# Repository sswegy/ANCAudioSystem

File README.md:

# ANCAudioSystem
## Автомобилна аудио система с активно шумопотискане - Дипломна работа

## Характеристики
- Активно шумопотискане
- Изравняване на звука по 3 честотни ленти
- Изравняване на противошума по 3 честотни ленти
- Bluetooth връзка
- AUX връзка
- Визуализация на метаданните на песните
- Контроли за промяна/пауза на песента

## Използвани технологии
- ESP32-WROOM-32
- C++
- Електроника

[Документация](https://docs.google.com/document/d/18OyuSNhzSNt5vsgb9MGb9Y_gkE6eRHnCl0IYLaxOIx8/edit?usp=sharing)

## Автор
[Виктор Велков](https://www.github.com/sswegy) 

Произведено во Света Троица

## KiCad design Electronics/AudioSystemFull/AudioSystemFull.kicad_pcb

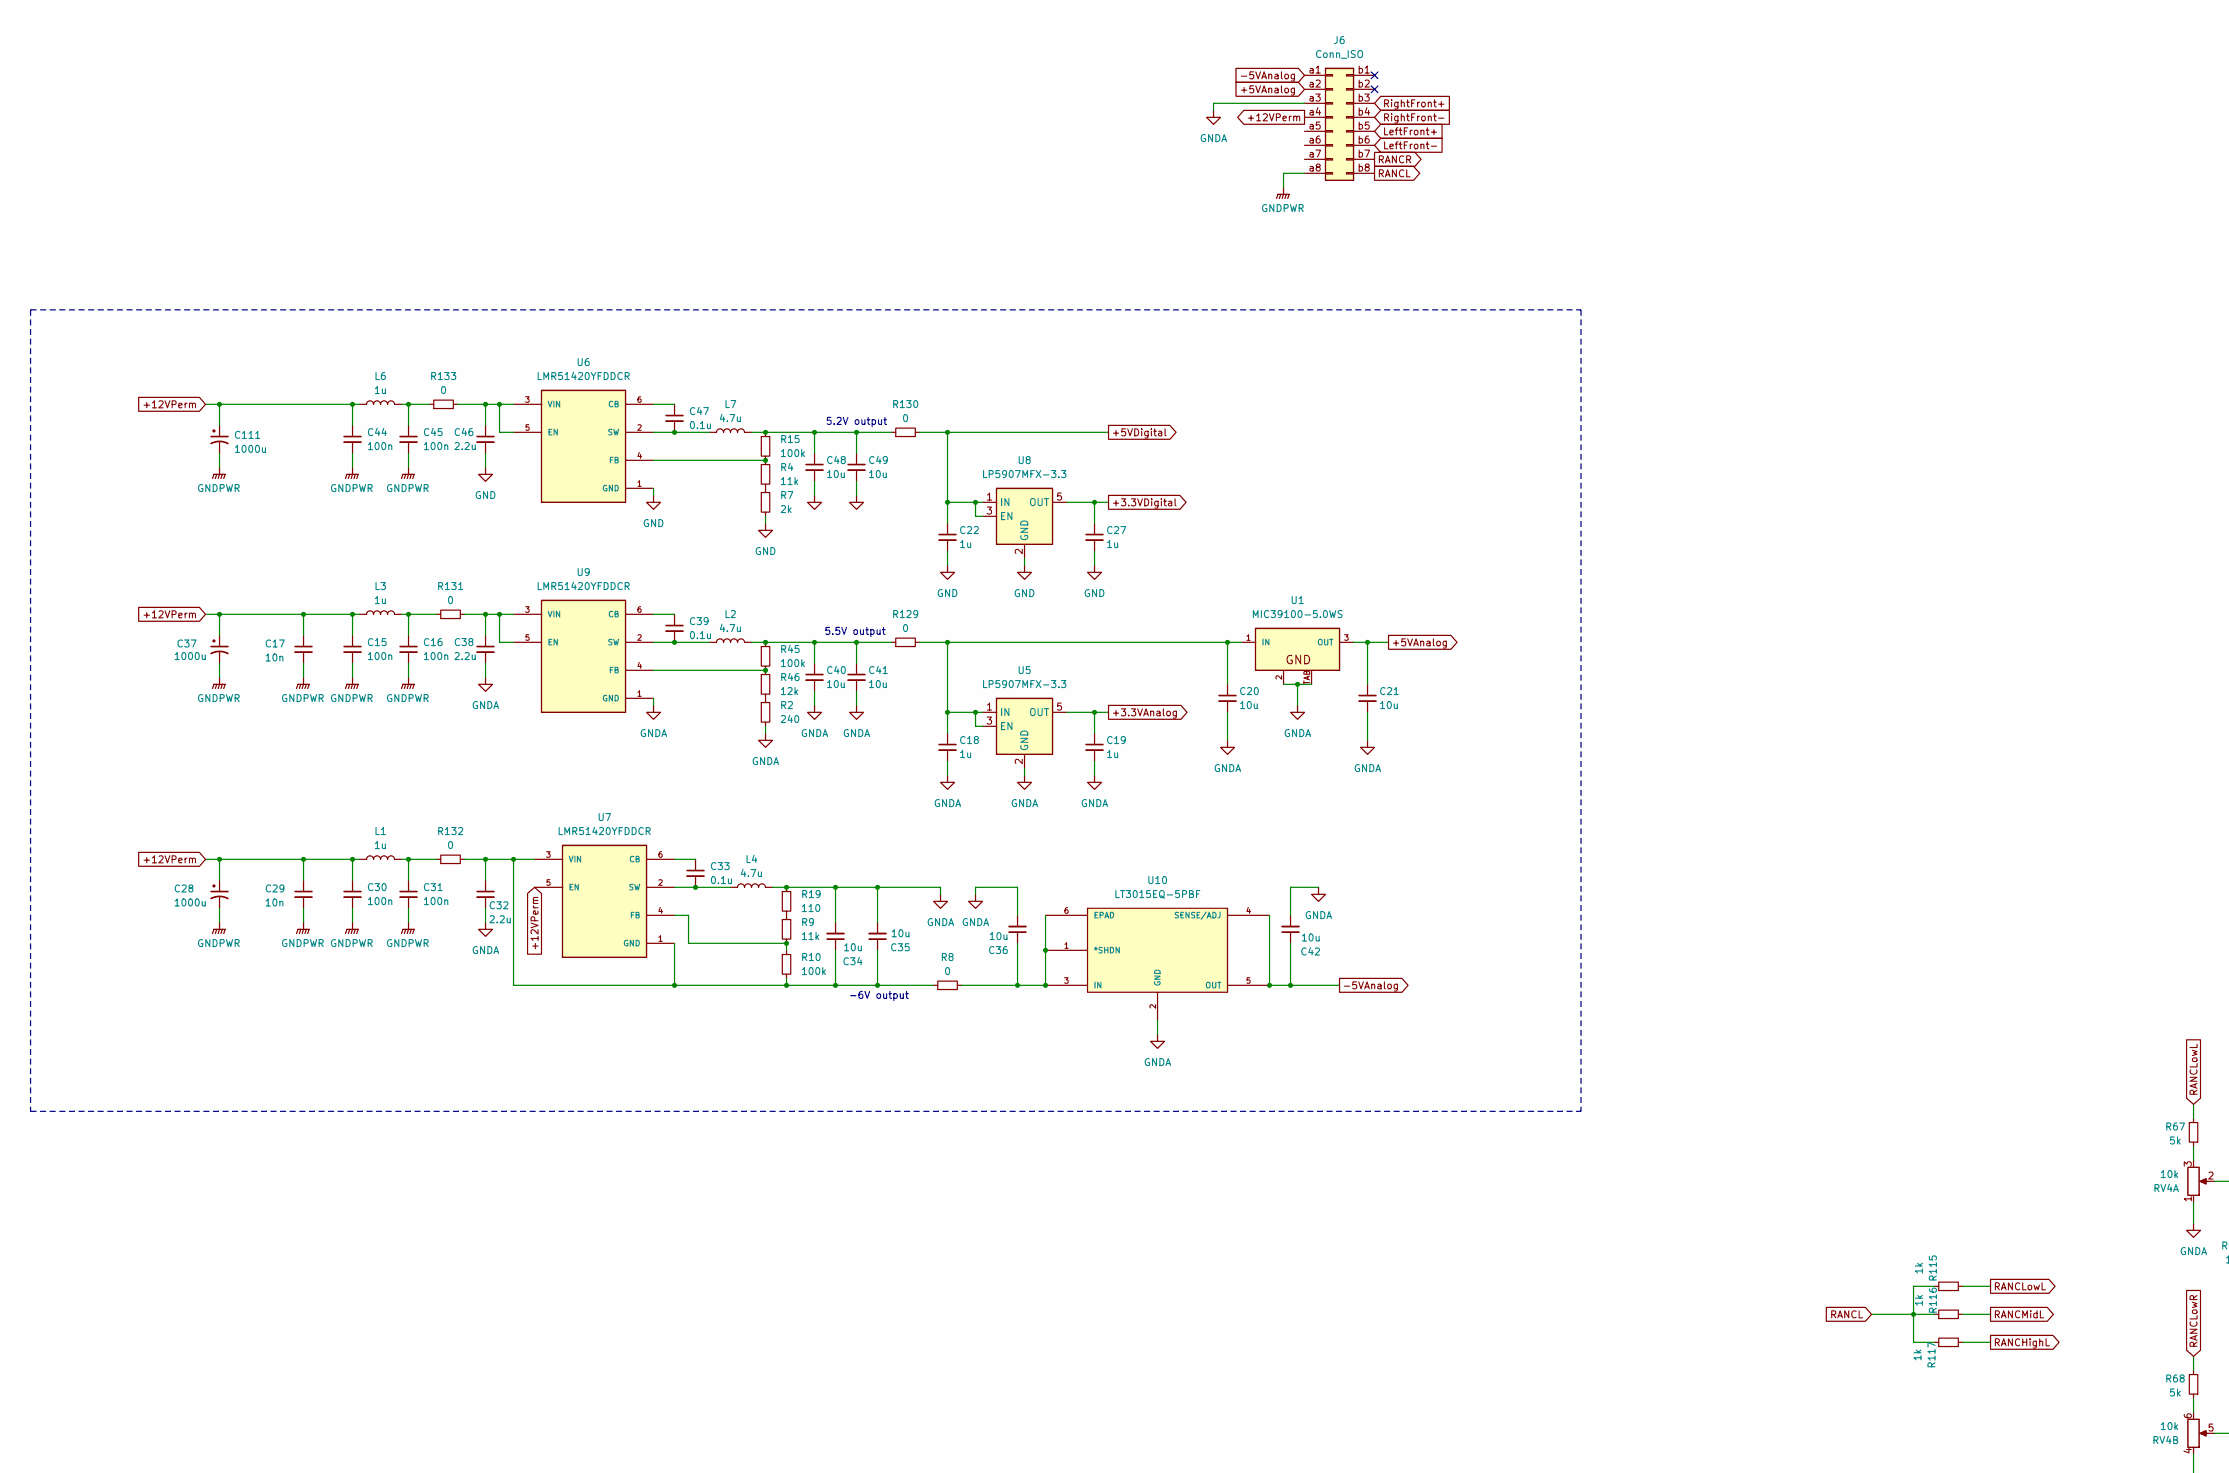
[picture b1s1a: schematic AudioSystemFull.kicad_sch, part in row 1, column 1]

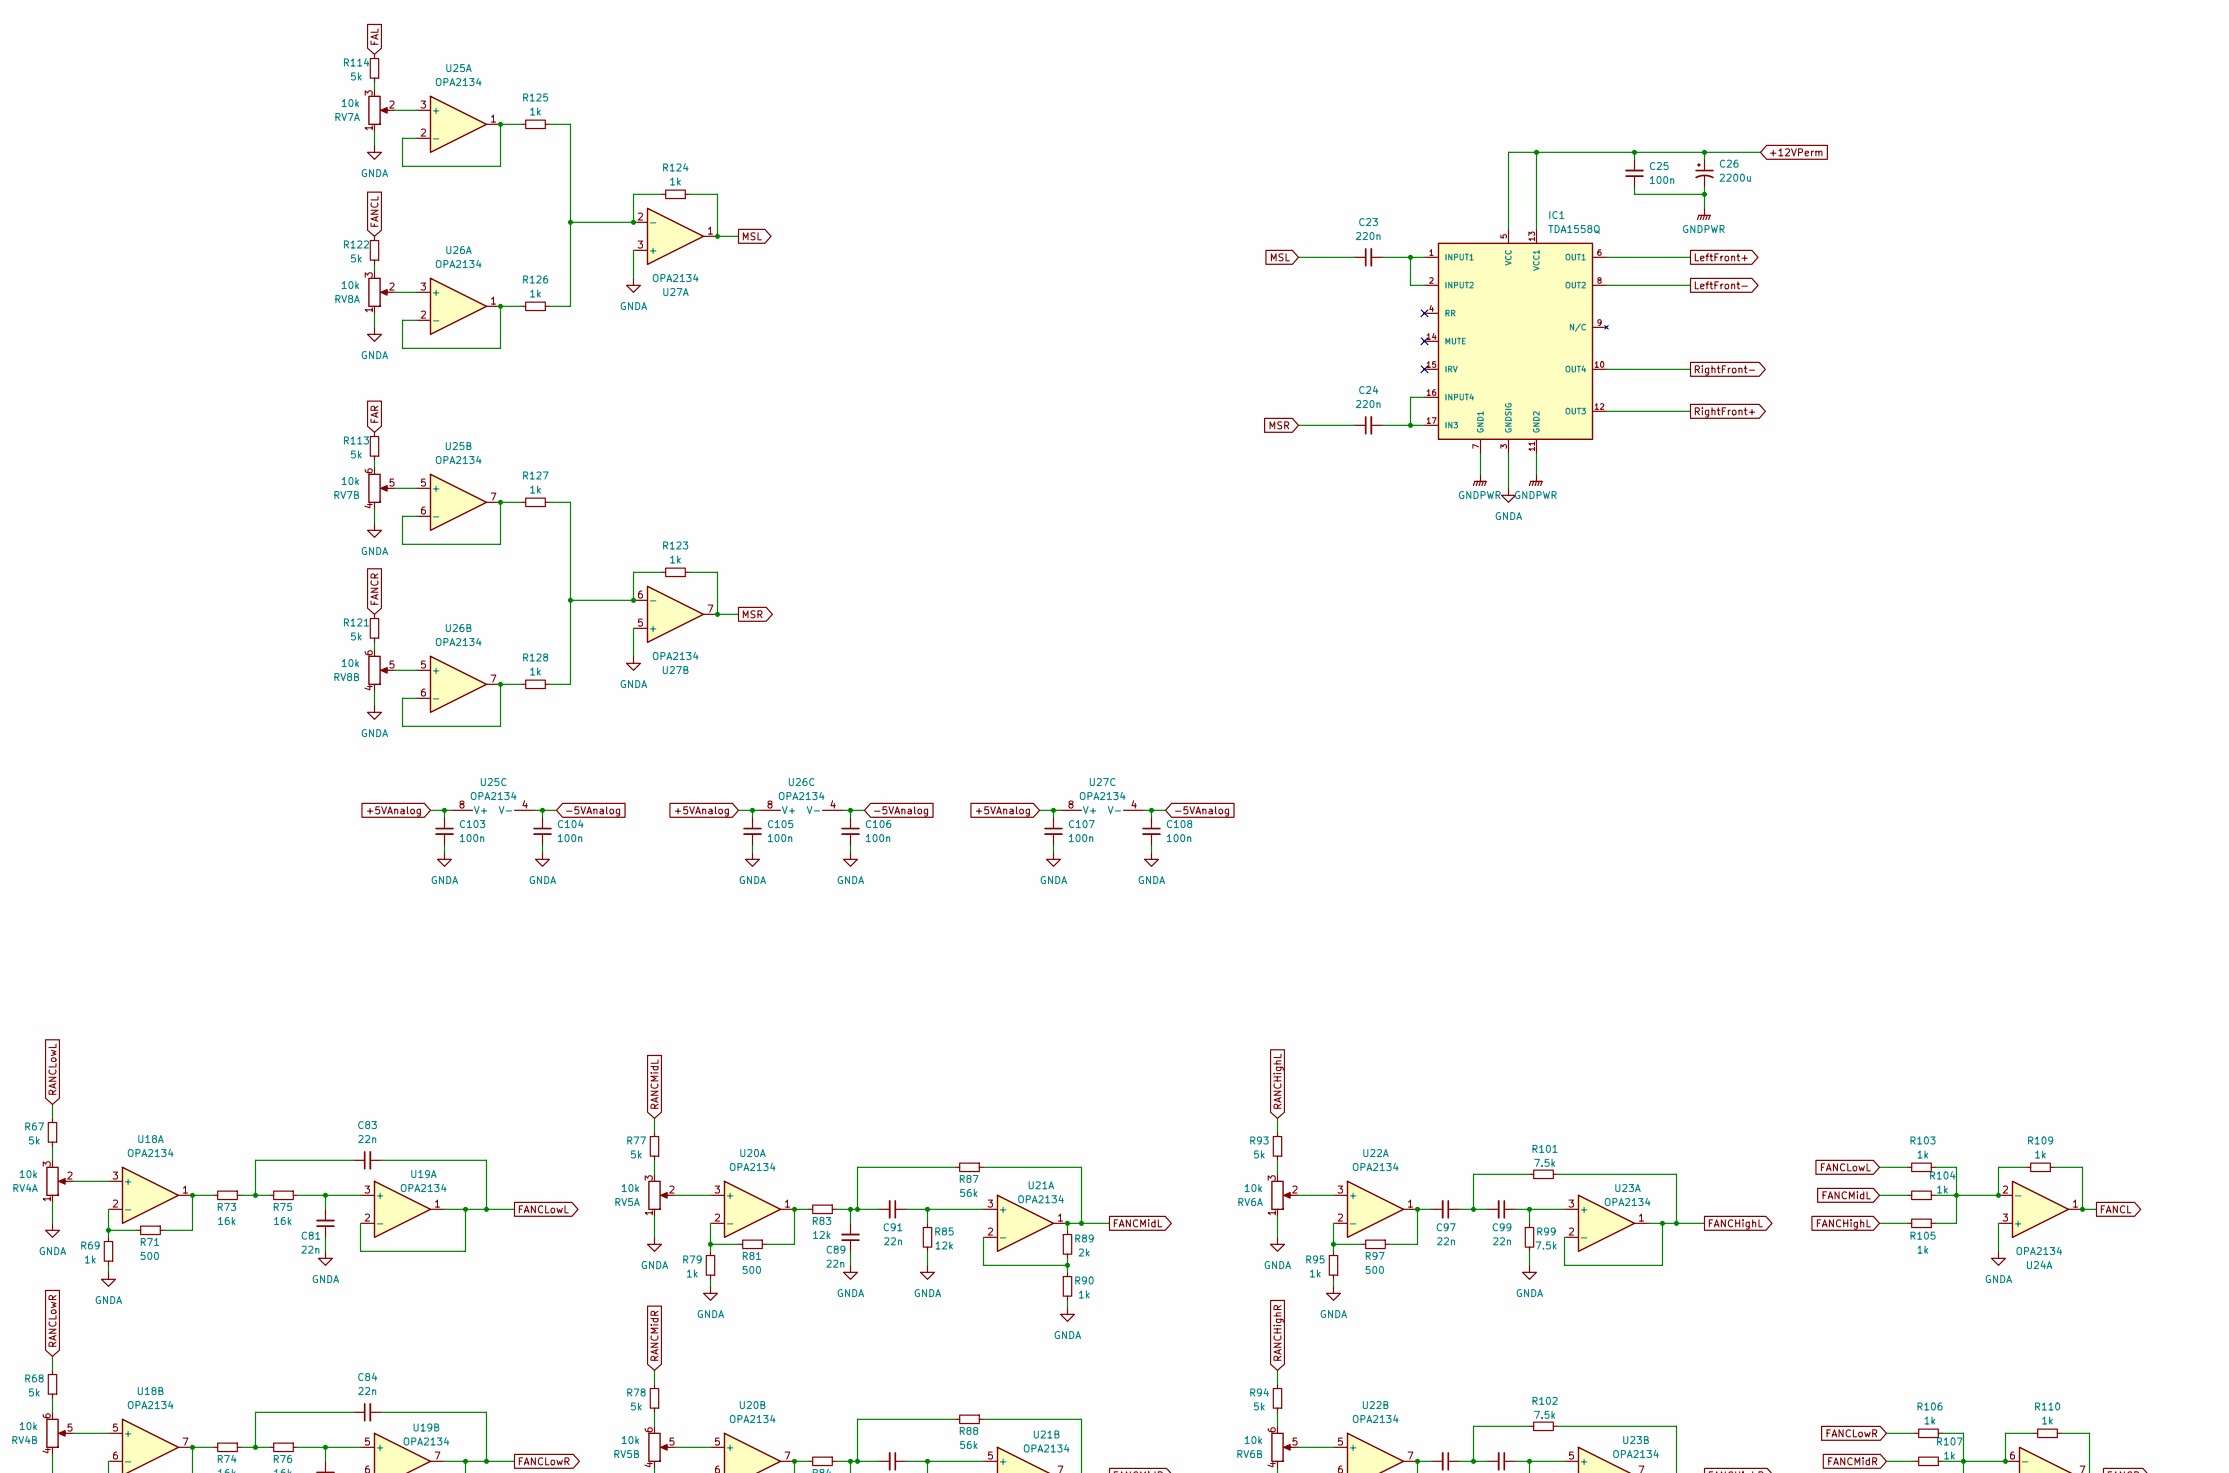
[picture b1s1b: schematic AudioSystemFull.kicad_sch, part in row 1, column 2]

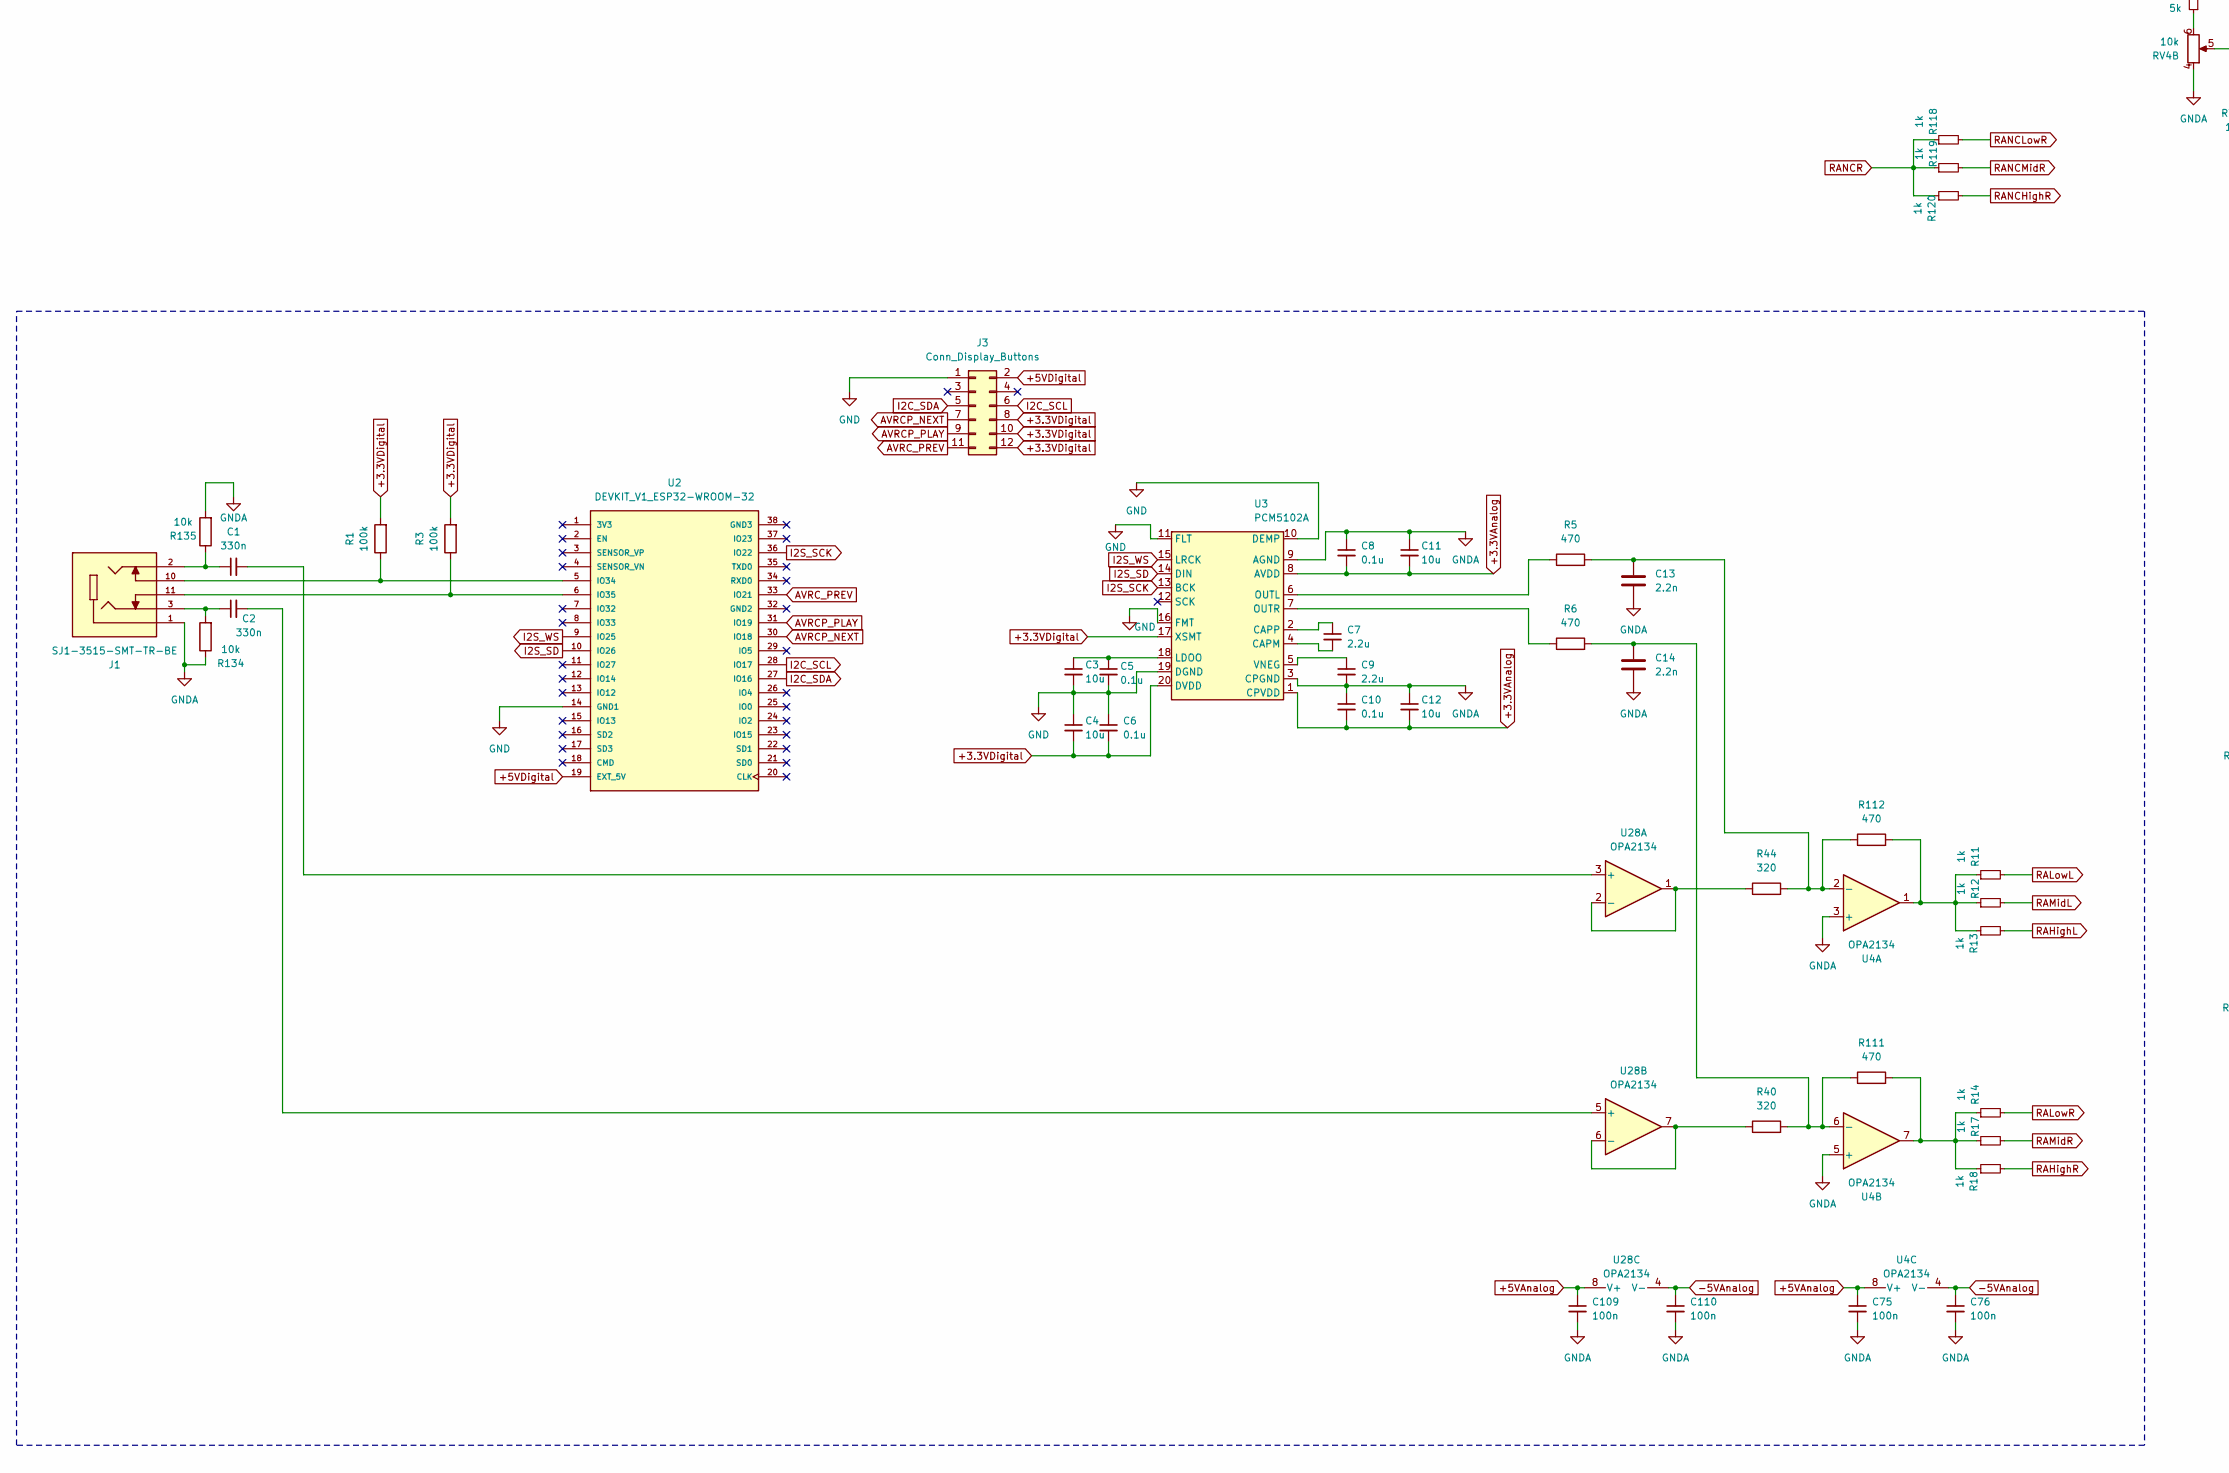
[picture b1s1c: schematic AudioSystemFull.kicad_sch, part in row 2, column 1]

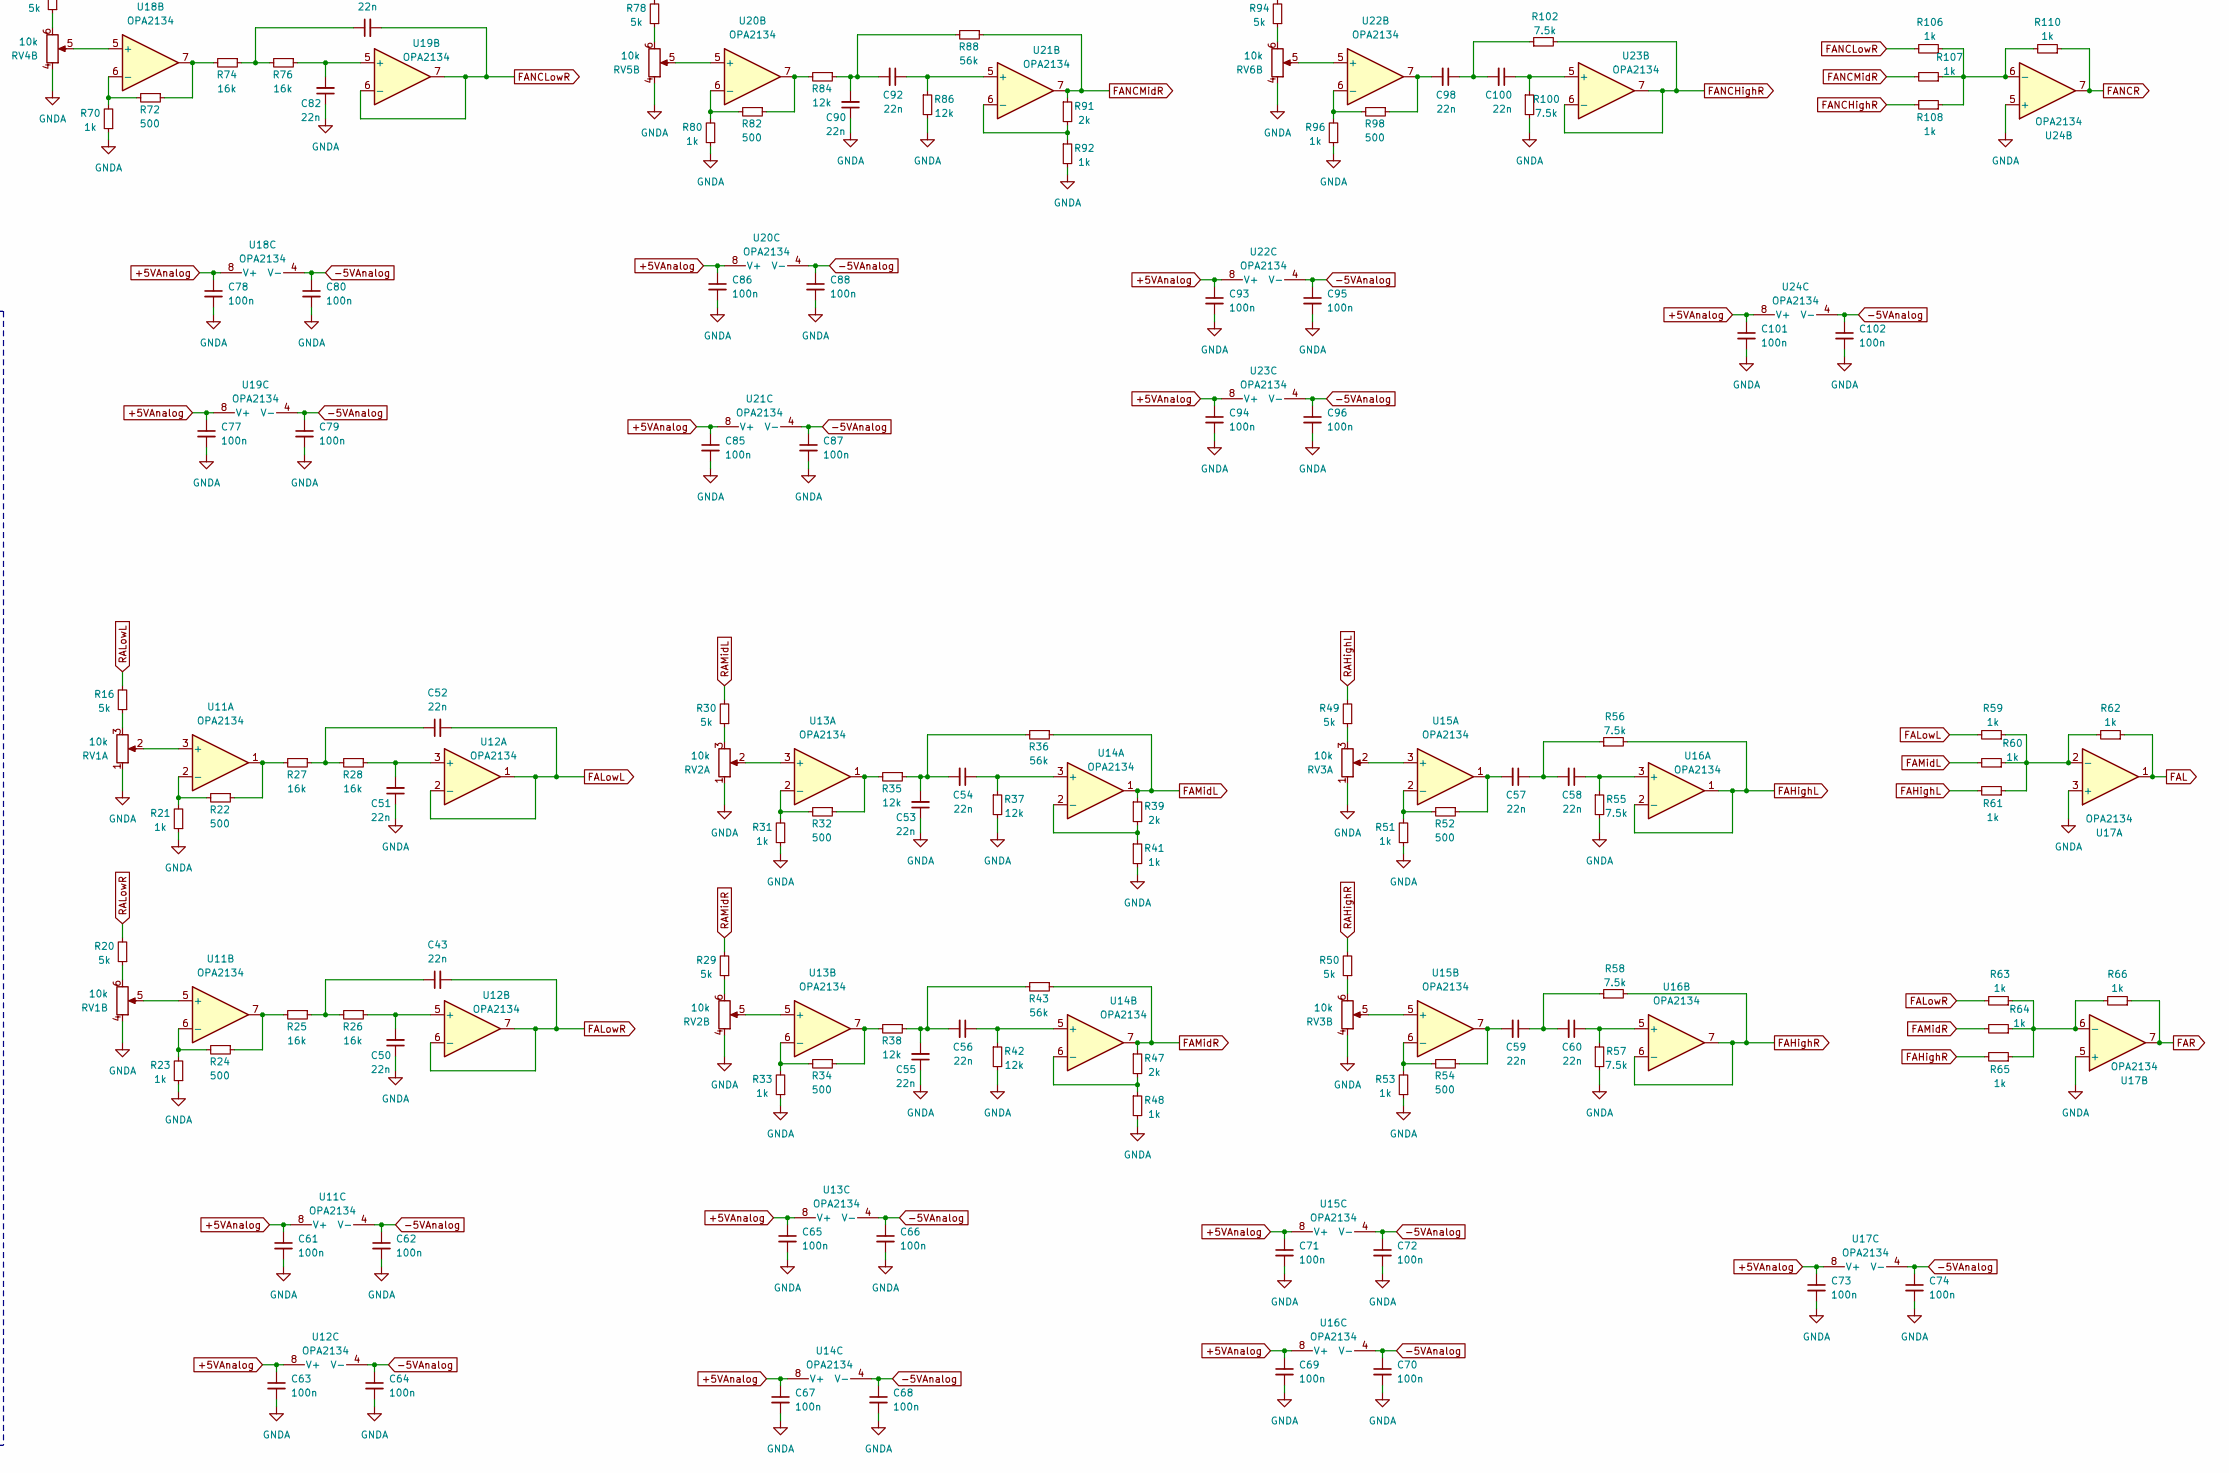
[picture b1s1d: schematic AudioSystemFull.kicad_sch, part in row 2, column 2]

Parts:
C1, C2: 330n; C_1206_3216Metric_Pad1.33x1.80mm_HandSolder; MANUFACTURER_PART_NUMBER GRM31C5C1E334JE01L
C3, C4, C11, C12, C20, C21, C34, C35, C36, C40, C41, C42, C48, C49: 10u; C_0805_2012Metric_Pad1.18x1.45mm_HandSolder; MANUFACTURER_PART_NUMBER GRM21BZ71E106KE15K
C5, C6, C8, C10, C33, C39, C47: 0.1u; C_0805_2012Metric_Pad1.18x1.45mm_HandSolder; MANUFACTURER_PART_NUMBER C0805C104K3RACTU
C7, C9, C32, C38, C46: 2.2u; C_0805_2012Metric_Pad1.18x1.45mm_HandSolder; MANUFACTURER_PART_NUMBER CC0805KKX7R9BB225
C13, C14: 2.2n; C_0805_2012Metric_Pad1.18x1.45mm_HandSolder; MANUFACTURER_PART_NUMBER C0805C222J5GACTU
C15, C16, C25, C30, C31, C44, C45, C61, C62, C63, C64, C65, C66, C67, C68, C69, C70, C71, C72, C73, C74, C75, C76, C77, C78, C79, C80, C85, C86, C87, C88, C93, C94, C95, C96, C101, C102, C103, C104, C105, C106, C107, C108, C109, C110: 100n; C_0805_2012Metric_Pad1.18x1.45mm_HandSolder; MANUFACTURER_PART_NUMBER C0805C104K3RACTU
C17, C29: 10n; C_0805_2012Metric_Pad1.18x1.45mm_HandSolder; MANUFACTURER_PART_NUMBER C0805C103K1RACTU
C18, C19, C22, C27: 1u; C_0805_2012Metric_Pad1.18x1.45mm_HandSolder; MANUFACTURER_PART_NUMBER C0805C105K3RACTU
C23, C24: 220n; C_1206_3216Metric_Pad1.33x1.80mm_HandSolder; MANUFACTURER_PART_NUMBER GRM31C5C1E224JE02L
C26: 2200u; CP_Radial_D12.5mm_P5.00mm; MANUFACTURER_PART_NUMBER EGPD350ELL222MK30H
C28, C37, C111: 1000u; CP_Radial_D12.5mm_P5.00mm; MANUFACTURER_PART_NUMBER UKT1V102MHD1TO
C43, C50, C51, C52, C53, C54, C55, C56, C57, C58, C59, C60, C81, C82, C83, C84, C89, C90, C91, C92, C97, C98, C99, C100: 22n; C_0805_2012Metric_Pad1.18x1.45mm_HandSolder; MANUFACTURER_PART_NUMBER C0805C223K5GEC7210
IC1: TDA1558Q; MANUFACTURER_PART_NUMBER TDA1558Q
J1: SJ1-3515-SMT-TR-BE; PARTREV 1.08
J3: Conn_Display_Buttons; Molex-43045-1211; MANUFACTURER_PART_NUMBER Molex-43045-1211
J6: Conn_ISO; Conn_ISO_Solder_Pad
L1, L3, L6: 1u; SRP5030T-1R0M; MANUFACTURER_PART_NUMBER SRP5030T-1R0M
L2, L4, L7: 4.7u; VLS6045EX-4R7M-H; MANUFACTURER_PART_NUMBER VLS6045EX-4R7M-H
R1, R3, R10, R15, R45: 100k; R_0805_2012Metric_Pad1.20x1.40mm_HandSolder; MANUFACTURER_PART_NUMBER RT0805FRE10100KL
R2: 240; R_0805_2012Metric_Pad1.20x1.40mm_HandSolder; MANUFACTURER_PART_NUMBER RT0805FRE07240RL
R4, R9: 11k; R_0805_2012Metric_Pad1.20x1.40mm_HandSolder; MANUFACTURER_PART_NUMBER RT0805FRE0711KL
R5, R6, R111, R112: 470; R_0805_2012Metric_Pad1.20x1.40mm_HandSolder; MANUFACTURER_PART_NUMBER RT0805DRD07470RL
R7, R39, R47, R89, R91: 2k; R_0805_2012Metric_Pad1.20x1.40mm_HandSolder; MANUFACTURER_PART_NUMBER RT0805FRE102KL
R8, R129, R130, R131, R132, R133: 0; R_0805_2012Metric_Pad1.20x1.40mm_HandSolder; MANUFACTURER_PART_NUMBER PT0805-R-070RL
R11, R12, R13, R14, R17, R18, R21, R23, R31, R33, R41, R48, R51, R53, R59, R60, R61, R62, R63, R64, R65, R66, R69, R70, R79, R80, R90, R92, R95, R96, R103, R104, R105, R106, R107, R108, R109, R110, R115, R116, R117, R118, R119, R120, R123, R124, R125, R126, R127, R128: 1k; R_0805_2012Metric_Pad1.20x1.40mm_HandSolder; MANUFACTURER_PART_NUMBER RT0805FRE071KL
R16, R20, R29, R30, R49, R50, R67, R68, R77, R78, R93, R94, R113, R114, R121, R122: 5k; R_0805_2012Metric_Pad1.20x1.40mm_HandSolder; MANUFACTURER_PART_NUMBER CRT0805-BY-5001EAS
R19: 110; R_0805_2012Metric_Pad1.20x1.40mm_HandSolder; MANUFACTURER_PART_NUMBER RT0805FRE07110RL
R22, R24, R32, R34, R52, R54, R71, R72, R81, R82, R97, R98: 500; R_0805_2012Metric_Pad1.20x1.40mm_HandSolder; MANUFACTURER_PART_NUMBER RN73R2ATTD5000B25
R25, R26, R27, R28, R73, R74, R75, R76: 16k; R_0805_2012Metric_Pad1.20x1.40mm_HandSolder; MANUFACTURER_PART_NUMBER RT0805FRE0716KL
R35, R37, R38, R42, R46, R83, R84, R85, R86: 12k; R_0805_2012Metric_Pad1.20x1.40mm_HandSolder; MANUFACTURER_PART_NUMBER RT0805FRE0712KL
R36, R43, R87, R88: 56k; R_0805_2012Metric_Pad1.20x1.40mm_HandSolder; MANUFACTURER_PART_NUMBER RT0805DRE0756KL
R40, R44: 320; R_0805_2012Metric_Pad1.20x1.40mm_HandSolder; MANUFACTURER_PART_NUMBER RT0805BRD07320RL
R55, R56, R57, R58, R99, R100, R101, R102: 7.5k; R_0805_2012Metric_Pad1.20x1.40mm_HandSolder; MANUFACTURER_PART_NUMBER RT0805FRE077K5L
R134, R135: 10k; R_0805_2012Metric_Pad1.20x1.40mm_HandSolder; MANUFACTURER_PART_NUMBER RT0805FRE1310KL
RV1, RV2, RV3, RV4, RV5, RV6, RV7, RV8: 10k; PTN092H10120K1B; MANUFACTURER_PART_NUMBER PTN092H10120K1B
U1: MIC39100-5.0WS; MANUFACTURER_PART_NUMBER MIC39100-5.0WS-TR
U2: DEVKIT_V1_ESP32-WROOM-32; MODULE_DEVKIT_V1_ESP32-WROOM-32; PARTREV N/A
U3: PCM5102A; TSSOP-20_4.4x6.5mm_P0.65mm; MANUFACTURER_PART_NUMBER PCM5102A
U4, U11, U12, U13, U14, U15, U16, U17, U18, U19, U20, U21, U22, U23, U24, U25, U26, U27, U28: OPA2134; OPA2134UA; MANUFACTURER_PART_NUMBER OPA2134UA
U5, U8: LP5907MFX-3.3; SOT-23-5; MANUFACTURER_PART_NUMBER LP5907MFX-3.3
U6, U7, U9: LMR51420YFDDCR; PARTREV C
U10: LT3015EQ-5PBF; MANUFACTURER_PART_NUMBER LT3015EQ-5PBF

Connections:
+3.3VAnalog: C8.2, C10.2, C11.2, C12.2, C19.1, U3.1 (CPVDD), U3.8 (AVDD), U5.5 (OUT)
+3.3VDigital: C4.2, C6.2, C27.1, J3.8, J3.10, J3.12, R1.2, R3.2, U3.17 (XSMT), U3.20 (DVDD), U8.5 (OUT)
+5VAnalog: C21.1, C61.1, C63.1, C65.1, C67.1, C69.1, C71.1, C73.1, C75.1, C77.1, C78.1, C85.1, C86.1, C93.1, C94.1, C101.1, C103.1, C105.1, C107.1, C109.1, J6.a2, U1.3 (OUT), U4.8 (V+), U11.8 (V+), U12.8 (V+), U13.8 (V+), U14.8 (V+), U15.8 (V+), U16.8 (V+), U17.8 (V+), U18.8 (V+), U19.8 (V+), U20.8 (V+), U21.8 (V+), U22.8 (V+), U23.8 (V+), U24.8 (V+), U25.8 (V+), U26.8 (V+), U27.8 (V+), U28.8 (V+)
+5VDigital: C22.1, J3.2, R130.2, U2.19 (EXT_5V), U8.1 (IN), U8.3 (EN)
+12VPerm: C15.1, C17.1, C25.2, C26.1, C28.1, C29.1, C30.1, C37.1, C44.1, C111.1, IC1.5 (VCC), IC1.13 (VCC1), J6.a4, L1.1, L3.1, L6.1, U7.5 (EN)
-5VAnalog: C42.1, C62.1, C64.1, C66.1, C68.1, C70.1, C72.1, C74.1, C76.1, C79.1, C80.1, C87.1, C88.1, C95.1, C96.1, C102.1, C104.1, C106.1, C108.1, C110.1, J6.a1, U4.4 (V-), U10.4 (SENSE/ADJ), U10.5 (OUT), U11.4 (V-), U12.4 (V-), U13.4 (V-), U14.4 (V-), U15.4 (V-), U16.4 (V-), U17.4 (V-), U18.4 (V-), U19.4 (V-), U20.4 (V-), U21.4 (V-), U22.4 (V-), U23.4 (V-), U24.4 (V-), U25.4 (V-), U26.4 (V-), U27.4 (V-), U28.4 (V-)
AVRCP_NEXT: J3.7, U2.30 (IO18)
AVRCP_PLAY: J3.9, U2.31 (IO19)
AVRC_PREV: J3.11, U2.33 (IO21)
FAHighL: R56.2, R61.2, U16.1, U16.2 (-)
FAHighR: R58.2, R65.2, U16.6 (-), U16.7
FAL: R62.1, R114.2, U17.1
FALowL: C52.2, R59.2, U12.1, U12.2 (-)
FALowR: C43.2, R63.2, U12.6 (-), U12.7
FAMidL: R36.1, R39.1, R60.2, U14.1
FAMidR: R43.1, R47.1, R64.2, U14.7
FANCHighL: R101.2, R105.2, U23.1, U23.2 (-)
FANCHighR: R102.2, R108.2, U23.6 (-), U23.7
FANCL: R109.1, R122.2, U24.1
FANCLowL: C83.2, R103.2, U19.1, U19.2 (-)
FANCLowR: C84.2, R106.2, U19.6 (-), U19.7
FANCMidL: R87.1, R89.1, R104.2, U21.1
FANCMidR: R88.1, R91.1, R107.2, U21.7
FANCR: R110.1, R121.2, U24.7
FAR: R66.1, R113.2, U17.7
GND: C3.2, C4.1, C5.2, C6.1, C22.2, C27.2, C46.2, C48.2, C49.2, J3.1, R7.2, U2.14 (GND1), U3.10 (DEMP), U3.11 (FLT), U3.16 (FMT), U3.19 (DGND), U6.1 (GND), U8.2 (GND), U8.4 (NC)
GNDA: C8.1, C9.2, C10.1, C11.1, C12.1, C13.2, C14.2, C18.2, C19.2, C20.2, C21.2, C32.2, C34.2, C35.2, C36.2, C38.2, C40.2, C41.2, C42.2, C50.1, C51.1, C53.1, C55.1, C61.2, C62.2, C63.2, C64.2, C65.2, C66.2, C67.2, C68.2, C69.2, C70.2, C71.2, C72.2, C73.2, C74.2, C75.2, C76.2, C77.2, C78.2, C79.2, C80.2, C81.1, C82.1, C85.2, C86.2, C87.2, C88.2, C89.1, C90.1, C93.2, C94.2, C95.2, C96.2, C101.2, C102.2, C103.2, C104.2, C105.2, C106.2, C107.2, C108.2, C109.2, C110.2, IC1.3 (GNDSIG), J1.1, J6.a3, L4.2, R2.2, R19.1, R21.1, R23.1, R31.1, R33.1, R37.2, R41.2, R42.2, R48.2, R51.1, R53.1, R55.2, R57.2, R69.1, R70.1, R79.1, R80.1, R85.2, R86.2, R90.2, R92.2, R95.1, R96.1, R99.2, R100.2, R134.1, R135.2, RV1.1, RV1.4, RV2.1, RV2.4, RV3.1, RV3.4, RV4.1, RV4.4, RV5.1, RV5.4, RV6.1, RV6.4, RV7.1, RV7.4, RV8.1, RV8.4, U1.2, U1.TAB, U3.3 (CPGND), U3.9 (AGND), U4.3 (+), U4.5 (+), U5.2 (GND), U5.4 (NC), U9.1 (GND), U10.2 (GND), U17.3 (+), U17.5 (+), U24.3 (+), U24.5 (+), U27.3 (+), U27.5 (+)
GNDPWR: C15.2, C16.2, C17.2, C25.1, C26.2, C28.2, C29.2, C30.2, C31.2, C37.2, C44.2, C45.2, C111.2, IC1.7 (GND1), IC1.11 (GND2), J6.a8
I2C_SCL: J3.6, U2.28 (IO17)
I2C_SDA: J3.5, U2.27 (IO16)
I2S_SCK: U2.36 (IO22), U3.13 (BCK)
I2S_SD: U2.10 (IO26), U3.14 (DIN)
I2S_WS: U2.9 (IO25), U3.15 (LRCK)
LeftFront+: IC1.6 (OUT1), J6.b5
LeftFront-: IC1.8 (OUT2), J6.b6
MSL: C23.1, R124.1, U27.1
MSR: C24.1, R123.1, U27.7
unnamed: C1.1, J1.2, R135.1
unnamed: C2.1, J1.3, R134.2
unnamed: C16.1, L3.2, R131.1
unnamed: C31.1, L1.2, R132.1
unnamed: C40.1, C41.1, L2.2, R45.1, R129.1
unnamed: C43.1, R25.1, R26.2
unnamed: C45.1, L6.2, R133.1
unnamed: C48.1, C49.1, L7.2, R15.1, R130.1
unnamed: C52.1, R27.1, R28.2
unnamed: C53.2, C54.2, R35.1, R36.2
unnamed: C55.2, C56.2, R38.1, R43.2
unnamed: C57.1, C58.2, R56.1
unnamed: C57.2, R52.1, U15.1
unnamed: C59.1, C60.2, R58.1
unnamed: C59.2, R54.1, U15.7
unnamed: C83.1, R73.1, R75.2
unnamed: C84.1, R74.1, R76.2
unnamed: C89.2, C91.2, R83.1, R87.2
unnamed: C90.2, C92.2, R84.1, R88.2
unnamed: C97.1, C99.2, R101.1
unnamed: C97.2, R97.1, U22.1
unnamed: C98.2, R98.1, U22.7
unnamed: C98.1, C100.2, R102.1
unnamed: C24.2, IC1.16 (INPUT4), IC1.17 (IN3)
unnamed: C23.2, IC1.1 (INPUT1), IC1.2 (INPUT2)
unnamed: R2.1, R46.2
unnamed: R4.2, R7.1
unnamed: R11.1, R12.1, R13.1, R112.2, U4.1
unnamed: R16.1, RV1.3
unnamed: R9.1, R19.2
unnamed: R20.1, RV1.6
unnamed: R22.1, R27.2, U11.1
unnamed: R24.1, R25.2, U11.7
unnamed: R29.1, RV2.6
unnamed: R30.1, RV2.3
unnamed: R32.1, R35.2, U13.1
unnamed: R34.1, R38.2, U13.7
unnamed: R49.1, RV3.3
unnamed: R50.1, RV3.6
unnamed: R67.1, RV4.3
unnamed: R68.1, RV4.6
unnamed: R71.1, R73.2, U18.1
unnamed: R72.1, R74.2, U18.7
unnamed: R77.1, RV5.3
unnamed: R78.1, RV5.6
unnamed: R81.1, R83.2, U20.1
unnamed: R82.1, R84.2, U20.7
unnamed: R93.1, RV6.3
unnamed: R94.1, RV6.6
unnamed: R14.1, R17.1, R18.1, R111.2, U4.7
unnamed: R113.1, RV7.6
unnamed: R114.1, RV7.3
unnamed: R121.1, RV8.6
unnamed: R122.1, RV8.3
unnamed: C18.1, C20.1, R129.2, U1.1 (IN), U5.1 (IN), U5.3 (EN)
unnamed: J1.10, R1.1, U2.5 (IO34)
unnamed: J1.11, R3.1, U2.6 (IO35)
unnamed: C7.2, U3.4 (CAPM)
unnamed: C7.1, U3.2 (CAPP)
unnamed: C3.1, C5.1, U3.18 (LDOO)
unnamed: R5.1, U3.6 (OUTL)
unnamed: R6.1, U3.7 (OUTR)
unnamed: C9.1, U3.5 (VNEG)
unnamed: C13.1, R5.2, R44.2, R112.1, U4.2 (-)
unnamed: C14.1, R6.2, R40.2, R111.1, U4.6 (-)
unnamed: C47.1, U6.6 (CB)
unnamed: C46.1, R133.2, U6.3 (VIN), U6.5 (EN)
unnamed: R4.1, R15.2, U6.4 (FB)
unnamed: C47.2, L7.1, U6.2 (SW)
unnamed: C33.1, U7.6 (CB)
unnamed: R9.2, R10.1, U7.4 (FB)
unnamed: C32.1, C34.1, C35.1, R8.1, R10.2, R132.2, U7.1 (GND), U7.3 (VIN)
unnamed: C33.2, L4.1, U7.2 (SW)
unnamed: C39.1, U9.6 (CB)
unnamed: C38.1, R131.2, U9.3 (VIN), U9.5 (EN)
unnamed: R45.2, R46.1, U9.4 (FB)
unnamed: C39.2, L2.1, U9.2 (SW)
unnamed: C36.1, R8.2, U10.1 (*SHDN), U10.3 (IN), U10.6 (EPAD)
unnamed: RV1.2, U11.3 (+)
unnamed: R21.2, R22.2, U11.2 (-)
unnamed: RV1.5, U11.5 (+)
unnamed: R23.2, R24.2, U11.6 (-)
unnamed: C51.2, R28.1, U12.3 (+)
unnamed: C50.2, R26.1, U12.5 (+)
unnamed: RV2.2, U13.3 (+)
unnamed: R31.2, R32.2, U13.2 (-)
unnamed: RV2.5, U13.5 (+)
unnamed: R33.2, R34.2, U13.6 (-)
unnamed: C54.1, R37.1, U14.3 (+)
unnamed: R39.2, R41.1, U14.2 (-)
unnamed: C56.1, R42.1, U14.5 (+)
unnamed: R47.2, R48.1, U14.6 (-)
unnamed: RV3.2, U15.3 (+)
unnamed: R51.2, R52.2, U15.2 (-)
unnamed: RV3.5, U15.5 (+)
unnamed: R53.2, R54.2, U15.6 (-)
unnamed: C58.1, R55.1, U16.3 (+)
unnamed: C60.1, R57.1, U16.5 (+)
unnamed: R59.1, R60.1, R61.1, R62.2, U17.2 (-)
unnamed: R63.1, R64.1, R65.1, R66.2, U17.6 (-)
unnamed: RV4.2, U18.3 (+)
unnamed: R69.2, R71.2, U18.2 (-)
unnamed: RV4.5, U18.5 (+)
unnamed: R70.2, R72.2, U18.6 (-)
unnamed: C81.2, R75.1, U19.3 (+)
unnamed: C82.2, R76.1, U19.5 (+)
unnamed: RV5.2, U20.3 (+)
unnamed: R79.2, R81.2, U20.2 (-)
unnamed: RV5.5, U20.5 (+)
unnamed: R80.2, R82.2, U20.6 (-)
unnamed: C91.1, R85.1, U21.3 (+)
unnamed: R89.2, R90.1, U21.2 (-)
unnamed: C92.1, R86.1, U21.5 (+)
unnamed: R91.2, R92.1, U21.6 (-)
unnamed: RV6.2, U22.3 (+)
unnamed: R95.2, R97.2, U22.2 (-)
unnamed: RV6.5, U22.5 (+)
unnamed: R96.2, R98.2, U22.6 (-)
unnamed: C99.1, R99.1, U23.3 (+)
unnamed: C100.1, R100.1, U23.5 (+)
unnamed: R103.1, R104.1, R105.1, R109.2, U24.2 (-)
unnamed: R106.1, R107.1, R108.1, R110.2, U24.6 (-)
unnamed: RV7.2, U25.3 (+)
unnamed: R125.2, U25.1, U25.2 (-)
unnamed: RV7.5, U25.5 (+)
unnamed: R127.2, U25.6 (-), U25.7
unnamed: RV8.2, U26.3 (+)
unnamed: R126.2, U26.1, U26.2 (-)
unnamed: RV8.5, U26.5 (+)
unnamed: R128.2, U26.6 (-), U26.7
unnamed: R124.2, R125.1, R126.1, U27.2 (-)
unnamed: R123.2, R127.1, R128.1, U27.6 (-)
unnamed: C1.2, U28.3 (+)
unnamed: R44.1, U28.1, U28.2 (-)
unnamed: C2.2, U28.5 (+)
unnamed: R40.1, U28.6 (-), U28.7
RAHighL: R13.2, R49.2
RAHighR: R18.2, R50.2
RALowL: R11.2, R16.2
RALowR: R14.2, R20.2
RAMidL: R12.2, R30.2
RAMidR: R17.2, R29.2
RANCHighL: R93.2, R117.2
RANCHighR: R94.2, R120.2
RANCL: J6.b8, R115.1, R116.1, R117.1
RANCLowL: R67.2, R115.2
RANCLowR: R68.2, R118.2
RANCMidL: R77.2, R116.2
RANCMidR: R78.2, R119.2
RANCR: J6.b7, R118.1, R119.1, R120.1
RightFront+: IC1.12 (OUT3), J6.b3
RightFront-: IC1.10 (OUT4), J6.b4

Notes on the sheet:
5.2V output
-6V output
5.5V output

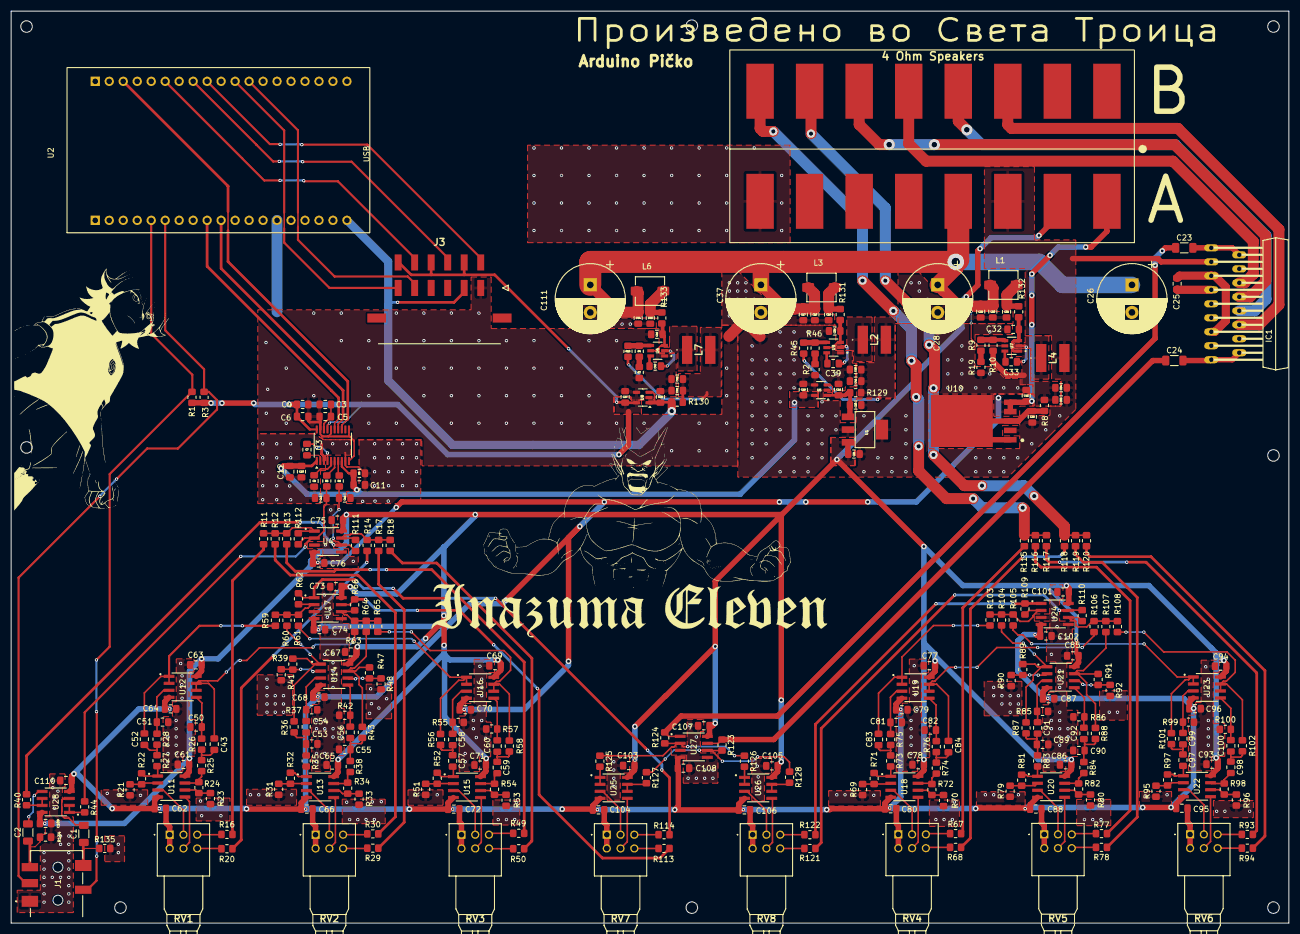
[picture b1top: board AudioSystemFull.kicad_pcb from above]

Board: 2 copper layers, 232.1 x 165.7 mm, 292 parts (0 on the bottom side), 189 nets.
